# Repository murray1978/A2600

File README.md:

# A2600
Atari 2600 clone/portable using period correct 6507, RIOT(6532) and a TIA(NTSC version).

## Changes to the original
- Removed the Audio subcarrier generator
- Removed the RF modulator

- Added a 74LS04 Clock generator
- Added RCA Video and Audio output

## Current Schematic
The current schematic references the Rev 14 and 15 schematics from the Feild Service Manual FD100133 Rev 02

## Current Board
Currently the board uses through hole components, in order to shrink the board even more I could go to a surface mount approach.
Pre fabrication check List, 
1. [ ] All gronds on ground plane connected
2. [ ] headers around the right way
3. [ ] VCC connected to components
4. [ ] correct footprints 
5. [ ] dont belive DRC in kicad

## Where to get parts

## Construction

## Trouble shooting

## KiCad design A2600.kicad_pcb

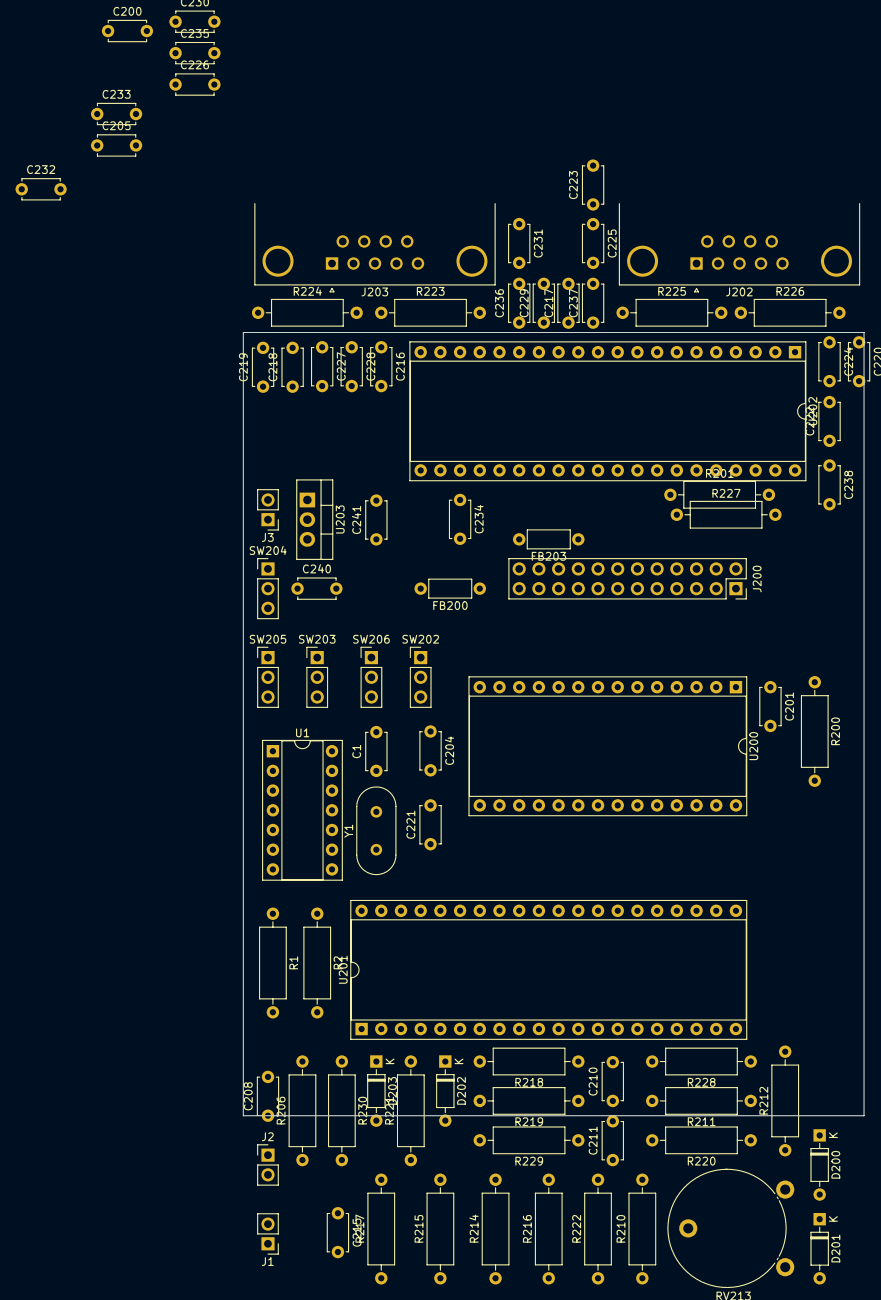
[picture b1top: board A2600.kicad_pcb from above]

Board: 2 copper layers, 80.0 x 101.0 mm, 83 parts (0 on the bottom side), 72 nets, no tracks yet.

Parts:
C1: 100p; C_Disc_D4.7mm_W2.5mm_P5.00mm
C200, C205, C208, C222, C236, C237, C238, C240: 100n; C_Disc_D4.7mm_W2.5mm_P5.00mm
C201: 4u7; C_Disc_D4.7mm_W2.5mm_P5.00mm
C204: 22n; C_Disc_D4.7mm_W2.5mm_P5.00mm
C210: 47p; C_Disc_D4.7mm_W2.5mm_P5.00mm
C211: 22p; C_Disc_D4.7mm_W2.5mm_P5.00mm
C215: 150p; C_Disc_D4.7mm_W2.5mm_P5.00mm
C216, C217: 470p; C_Disc_D4.7mm_W2.5mm_P5.00mm
C218, C219, C220, C221: 68p; C_Disc_D4.7mm_W2.5mm_P5.00mm
C223, C224, C225, C226, C227, C228, C229, C230: 1p; C_Disc_D4.7mm_W2.5mm_P5.00mm
C231, C232, C233, C234, C235: 1n; C_Disc_D4.7mm_W2.5mm_P5.00mm
C241: 1u; C_Disc_D4.7mm_W2.5mm_P5.00mm
D200, D201, D202, D203: 1N914; D_DO-35_SOD27_P7.62mm_Horizontal
FB200, FB203: Ferrite_Bead; L_Axial_L5.3mm_D2.2mm_P7.62mm_Horizontal_Vishay_IM-1
J1: VIDEO; PinHeader_1x02_P2.54mm_Vertical
J2: AUDIO; PinHeader_1x02_P2.54mm_Vertical
J3: 9V; PinHeader_1x02_P2.54mm_Vertical
J200: Cartridge; PinSocket_2x12_P2.54mm_Vertical
J202: Paddle_One; DSUB-9_Female_Horizontal_P2.77x2.84mm_EdgePinOffset4.94mm_H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
J203: Paddle_Two; DSUB-9_Female_Horizontal_P2.77x2.84mm_EdgePinOffset4.94mm_H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
R1, R2, R206, R211, R228: 1K; R_Axial_DIN0309_L9.0mm_D3.2mm_P12.70mm_Horizontal
R200, R217, R227: 24K; R_Axial_DIN0309_L9.0mm_D3.2mm_P12.70mm_Horizontal
R201, R212, R219, R221: 4K7; R_Axial_DIN0309_L9.0mm_D3.2mm_P12.70mm_Horizontal
R210: 6k8; R_Axial_DIN0309_L9.0mm_D3.2mm_P12.70mm_Horizontal
R214: 27K; R_Axial_DIN0309_L9.0mm_D3.2mm_P12.70mm_Horizontal
R215: 47K; R_Axial_DIN0309_L9.0mm_D3.2mm_P12.70mm_Horizontal
R216: 110K; R_Axial_DIN0309_L9.0mm_D3.2mm_P12.70mm_Horizontal
R218, R220: 3K3; R_Axial_DIN0309_L9.0mm_D3.2mm_P12.70mm_Horizontal
R222: 15K; R_Axial_DIN0309_L9.0mm_D3.2mm_P12.70mm_Horizontal
R223, R229, R230: 10K; R_Axial_DIN0309_L9.0mm_D3.2mm_P12.70mm_Horizontal
R224, R225: 220R; R_Axial_DIN0309_L9.0mm_D3.2mm_P12.70mm_Horizontal
R226: 10k; R_Axial_DIN0309_L9.0mm_D3.2mm_P12.70mm_Horizontal
RV213: 500K; Potentiometer_Piher_PT-15-V02_Vertical
SW202: RESET; PinHeader_1x03_P2.54mm_Vertical
SW203: SELECT; PinHeader_1x03_P2.54mm_Vertical
SW204: B/W; PinHeader_1x03_P2.54mm_Vertical
SW205: Left Dif; PinHeader_1x03_P2.54mm_Vertical
SW206: RIGHT Dif; PinHeader_1x03_P2.54mm_Vertical
U1: 74LS04; DIP-14_W7.62mm_Socket
U200: R6507; DIP-28_W15.24mm_Socket
U201: TIA; DIP-40_W15.24mm_Socket
U202: 6532; DIP-40_W15.24mm_Socket
U203: L7805; TO-220-3_Vertical
Y1: 3.59545Mhz; Crystal_HC49-U_Vertical

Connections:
+9V: C241.2, J3.2, R212.2, U203.1
/A0: J200.8, U200.5, U201.32, U202.7
/A1: J200.7, U200.6, U201.31, U202.6
/A2: J200.6, U200.7, U201.30, U202.5
/A3: J200.5, U200.8, U201.29, U202.4
/A4: J200.4, U200.9, U201.27, U201.28, U202.2, U202.3
/A5: J200.3, U200.10
/A6: J200.2, U200.11, U202.40
/A7: J200.1, U200.12, U201.21, U202.38
/A8: J200.22, U200.13
/A9: J200.21, U200.14, U202.36
/A10: J200.19, U200.15
/A11: J200.20, U200.16
/A12: J200.18, U200.17, U201.24, U202.37
/D0: J200.9, U200.25, U201.14, U202.33
/D1: J200.10, U200.24, U201.15, U202.32
/D2: J200.11, U200.23, U201.16, U202.31
/D3: J200.13, U200.22, U201.17, U202.30
/D4: J200.14, U200.21, U201.18, U202.29
/D5: J200.15, U200.20, U201.19, U202.28
/D6: J200.16, U200.19, U201.33, U202.27
/D7: J200.17, U200.18, U201.34, U202.26
/PA0: C223.1, J202.1, U202.8
/PA1: C224.1, J202.2, U202.9
/PA2: C225.1, J202.3, U202.10
/PA3: C226.1, J202.4, U202.11
/PA4: C227.1, J203.1, U202.12
/PA5: C228.1, J203.2, U202.13
/PA6: C229.1, J203.3, U202.14
/PA7: C230.1, J203.4, U202.15
AnalogP1: R225.2, R226.1, U201.35
AnalogP2: R223.1, R224.2, U201.36
CADJ: C205.2, RV213.2, U201.10
GND: C200.2, C201.2, C204.2, C205.1, C215.1, C216.2, C217.2, C218.1, C218.2, C219.2, C220.2, C221.2, C222.2, C223.2, C224.2, C225.2, C226.2, C227.2, C228.2, C229.2, C230.2, C231.2, C232.2, C233.2, C234.2, C235.2, C236.2, C237.2, C238.2, C240.1, C241.1, FB203.2, J1.2, J2.2, J3.1, J200.24, J202.8, J203.5, J203.8, R222.2, RV213.1, SW202.2, SW203.2, SW204.2, SW205.2, SW206.2, U1.7, U200.2, U201.1, U201.22, U201.40, U202.1, U203.2
unnamed: C1.1, R1.1, U1.13
unnamed: C1.2, R2.2, U1.10
unnamed: C201.1, R200.1, U200.1
unnamed: C208.1, J2.1
unnamed: C208.2, R206.1, U201.12, U201.13
unnamed: C210.1, C211.2, R211.2
unnamed: C210.2, R228.2, U201.9
unnamed: C211.1, R210.2
unnamed: C215.2, J1.1, R210.1, R214.1, R215.1, R216.1, R217.1, R222.1
unnamed: C216.1, J203.6, R224.1
unnamed: C217.1, J202.6, R225.1
unnamed: C219.1, J203.9, U201.39
unnamed: C220.1, J202.5, U201.38
unnamed: C221.1, J202.9, U201.37
unnamed: C231.1, SW206.1, U202.16
unnamed: C232.1, SW205.1, U202.17
unnamed: C233.1, SW204.1, U202.21
unnamed: C234.1, SW202.1, U202.23
unnamed: C235.1, SW203.1, U202.24
unnamed: C238.1, R227.1, U202.34
unnamed: D200.2, D201.1
unnamed: D201.2, R212.1, RV213.3
unnamed: D202.1, R219.2, U201.5
unnamed: D202.2, R215.2, R229.2
unnamed: D203.1, R221.2, U201.2
unnamed: D203.2, R217.2, R230.2
unnamed: FB200.2, J200.23
unnamed: FB203.1, J200.12
unnamed: R1.2, U1.9, U1.12, Y1.1
unnamed: R2.1, U1.11, Y1.2
unnamed: R201.1, U200.3, U201.3
unnamed: R214.2, R218.2, U201.7
unnamed: R216.2, R220.2, U201.8
unnamed: U200.26, U201.25, U202.35
unnamed: U200.27, U201.4
unnamed: U200.28, U201.26, U202.39
OSC: U1.8, U201.11
VCC: C200.1, C204.1, C222.1, C236.1, C237.1, C240.2, D200.1, FB200.1, J202.7, J203.7, R200.2, R201.2, R206.2, R211.1, R218.1, R219.1, R220.1, R221.1, R223.2, R226.2, R227.2, R228.1, R229.1, R230.1, U1.14, U200.4, U201.20, U201.23, U202.20, U203.3

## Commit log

2020-11-02 Add files via upload
    initial commit
2020-11-03 Update README.md
    Creating readme
2020-11-03 Update README.md
    Update of Readme
2020-11-05 Update README.md
    added check list
2020-11-05 Update README.md
    corrected check list
